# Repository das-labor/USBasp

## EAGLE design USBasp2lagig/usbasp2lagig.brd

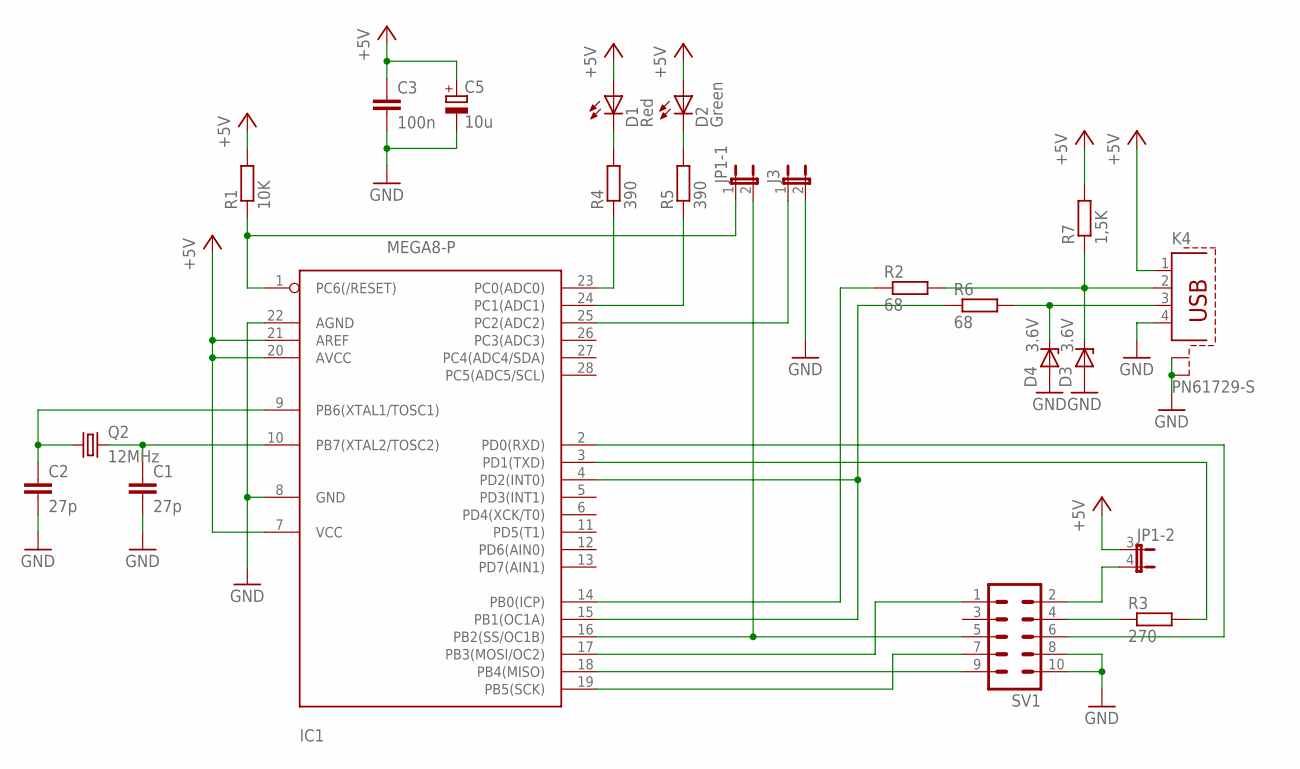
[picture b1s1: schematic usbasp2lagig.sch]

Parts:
C1, C2: 27p; C025-024X044
C3: 100n; C5B3
C5: 10u; E2,5-5
D1: Red; LED5MM
D2: Green; LED5MM
D3, D4: 3.6V; DO34Z7
IC1: MEGA8-P; DIL28-3
J3: JP1E; JP1
JP1: JP2QE; JP2Q
K4: PN61729-S
Q2: 12MHz; HC49/S
R1: 10K; 0207/7
R2, R6: 68; 0207/7
R3: 270; 0207/7
R4, R5: 390; 0207/7
R7: 1,5K; 0207/7
SV1: ML10LANG; ML10_LANG

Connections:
+5V: C3.1, C5.+, D1.A, D2.A, IC1.7 (VCC), IC1.20 (AVCC), IC1.21 (AREF), JP1.3 (1), K4.1, R1.2, R7.2
GND: C1.2, C2.2, C3.2, C5.-, D3.A, D4.A, IC1.8 (GND), IC1.22 (AGND), J3.2, K4.4, K4.S1, K4.S2, SV1.8, SV1.10
unnamed: D3.C, K4.2, R2.2, R7.1
unnamed: D4.C, K4.3, R6.2
unnamed: C1.1, IC1.10 (PB7(XTAL2/TOSC2)), Q2.2
unnamed: C2.1, IC1.9 (PB6(XTAL1/TOSC1)), Q2.1
unnamed: JP1.4 (2), SV1.2
unnamed: R3.1, SV1.4
unnamed: IC1.3 (PD1(TXD)), R3.2
unnamed: IC1.2 (PD0(RXD)), SV1.6
unnamed: IC1.17 (PB3(MOSI/OC2)), SV1.1
unnamed: IC1.18 (PB4(MISO)), SV1.9
unnamed: IC1.16 (PB2(SS/OC1B)), JP1.2, SV1.5
unnamed: IC1.1 (PC6(/RESET)), JP1.1, R1.1
unnamed: IC1.14 (PB0(ICP)), R2.1
unnamed: IC1.25 (PC2(ADC2)), J3.1
unnamed: IC1.23 (PC0(ADC0)), R4.1
unnamed: IC1.24 (PC1(ADC1)), R5.1
unnamed: IC1.4 (PD2(INT0)), IC1.15 (PB1(OC1A)), R6.1
unnamed: D1.K (C), R4.2
unnamed: D2.K (C), R5.2
unnamed: IC1.19 (PB5(SCK)), SV1.7

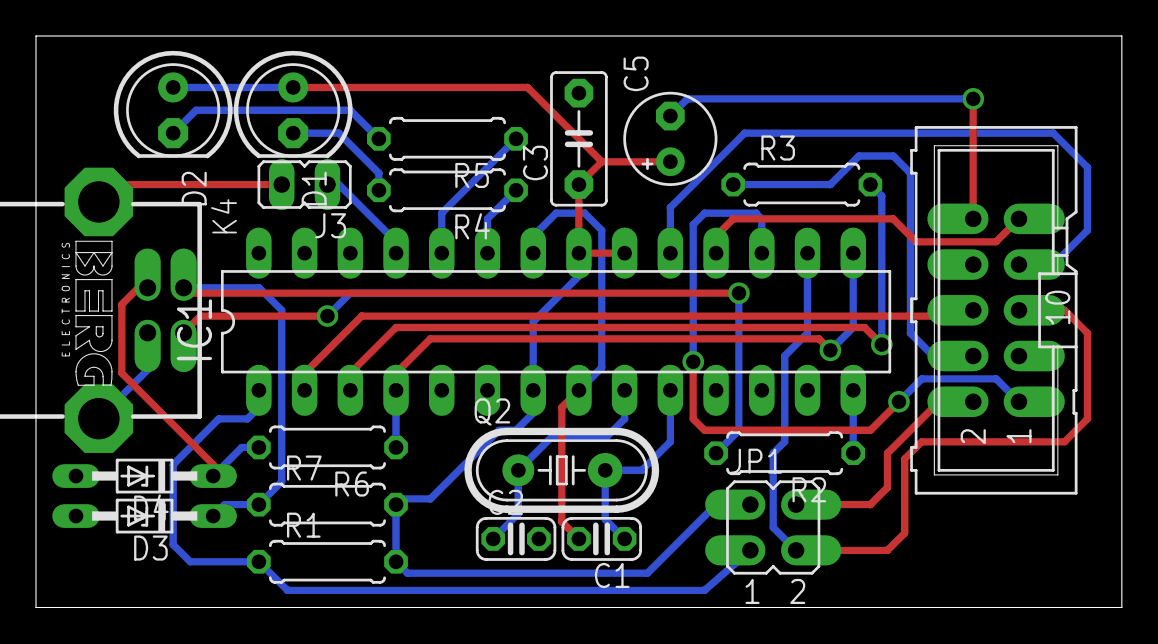
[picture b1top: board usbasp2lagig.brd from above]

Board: 2 copper layers, 60.3 x 31.8 mm, 21 parts (0 on the bottom side), 22 nets.

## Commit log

2015-05-01 new files
2015-05-01 two layer layout added
